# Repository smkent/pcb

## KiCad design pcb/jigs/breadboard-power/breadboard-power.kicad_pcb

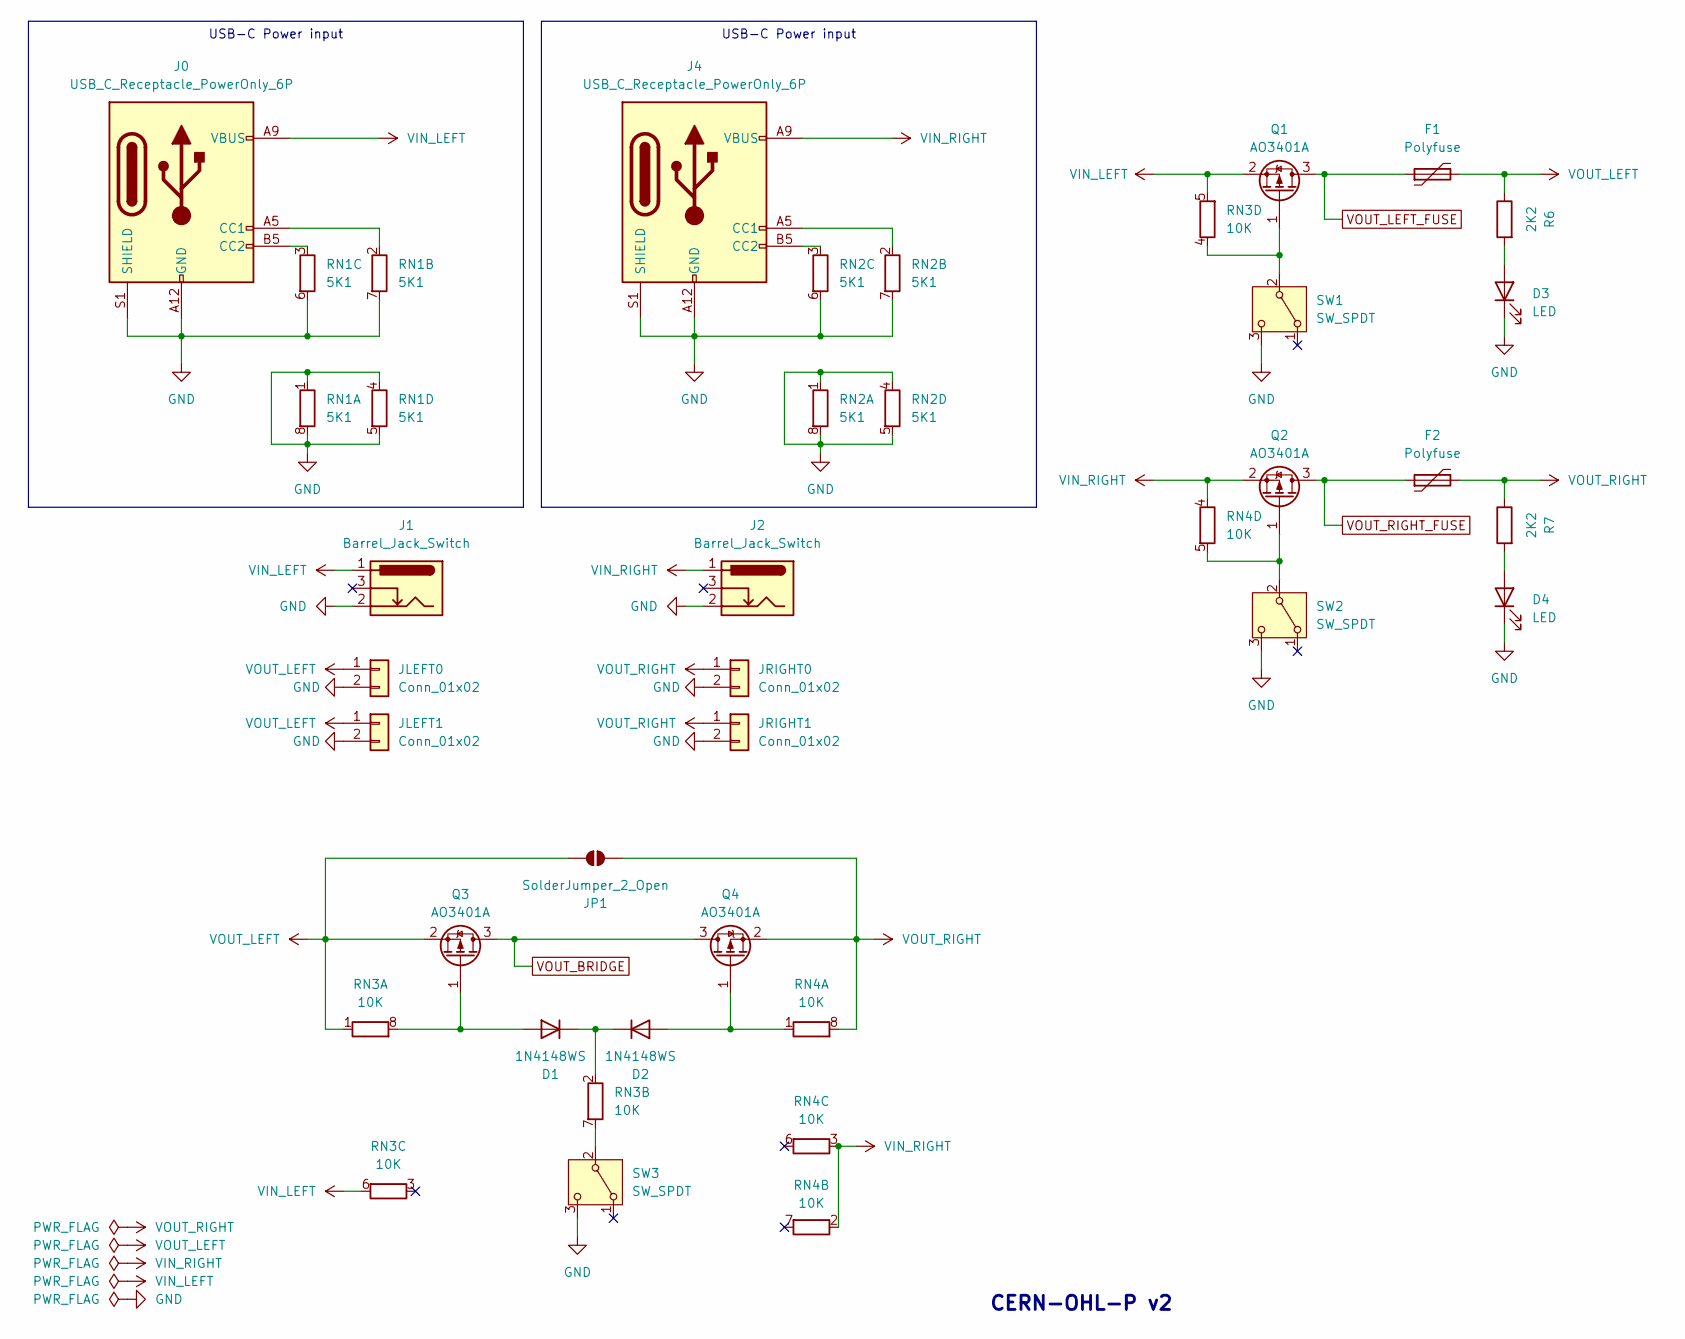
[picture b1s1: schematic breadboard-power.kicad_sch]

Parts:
D1, D2: 1N4148WS; D_SOD-323_HandSoldering
D3, D4: LED; LED_0805_2012Metric_Pad1.15x1.40mm_HandSolder_simple
F1, F2: Polyfuse; Fuse_1206_3216Metric
J0, J4: USB_C_Receptacle_PowerOnly_6P; USB_C_Receptacle_GCT_USB4125-xx-x_6P_TopMnt_Horizontal_Hand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
J1, J2: Barrel_Jack_Switch; Conn_Combo_DC-050_TerminalBlock_JST-XH-2P-horizontal-TH-or-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
JLEFT0, JLEFT1: Conn_01x02; PinHeader_1x02_P2.54mm_Vertical_simple_pad2gnd
JP1: SolderJumper_2_Open; SolderJumper-2_P1.3mm_Open_RoundedPad1.0x1.5mm_simple
JRIGHT0, JRIGHT1: Conn_01x02; PinHeader_1x02_P2.54mm_Vertical_simple_pad2gnd
Q1, Q2, Q3, Q4: AO3401A; SOT-23; LCSC Part C15127
R6, R7: 2K2; R_0805_2012Metric_Pad1.20x1.40mm_HandSolder
RN1, RN2: 5K1; R_Array_Convex_4x0603
RN3, RN4: 10K; R_Array_Convex_4x0603
SW1, SW2: SW_SPDT; SW_Slide-03_SPDT_P2.50mm_THT; LCSC Part C2998803
SW3: SW_SPDT; SW_SPDT_PCM12; LCSC Part C2998803

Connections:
GND: D3.1 (K), D4.1 (K), J0.A12 (GND), J0.B12 (GND), J0.S1 (SHIELD), J1.2, J2.2, J4.A12 (GND), J4.B12 (GND), J4.S1 (SHIELD), JLEFT0.2, JLEFT1.2, JRIGHT0.2, JRIGHT1.2, RN1.1 (R1.1), RN1.4 (R4.1), RN1.5 (R4.2), RN1.6 (R3.2), RN1.7 (R2.2), RN1.8 (R1.2), RN2.1 (R1.1), RN2.4 (R4.1), RN2.5 (R4.2), RN2.6 (R3.2), RN2.7 (R2.2), RN2.8 (R1.2), SW1.3 (C), SW2.3 (C), SW3.3 (C)
unnamed: D1.2 (A), Q3.1 (G), RN3.8 (R1.2)
unnamed: D1.1 (K), D2.1 (K), RN3.2 (R2.1)
unnamed: D2.2 (A), Q4.1 (G), RN4.1 (R1.1)
unnamed: D3.2 (A), R6.2
unnamed: D4.2 (A), R7.2
unnamed: J0.A5 (CC1), RN1.2 (R2.1)
unnamed: J0.B5 (CC2), RN1.3 (R3.1)
unnamed: J4.A5 (CC1), RN2.2 (R2.1)
unnamed: J4.B5 (CC2), RN2.3 (R3.1)
unnamed: Q1.1 (G), RN3.4 (R4.1), SW1.2 (B)
unnamed: Q2.1 (G), RN4.5 (R4.2), SW2.2 (B)
unnamed: RN3.7 (R2.2), SW3.2 (B)
VIN_LEFT: J0.A9 (VBUS), J0.B9 (VBUS), J1.1, Q1.2 (S), RN3.5 (R4.2), RN3.6 (R3.2)
VIN_RIGHT: J2.1, J4.A9 (VBUS), J4.B9 (VBUS), Q2.2 (S), RN4.2 (R2.1), RN4.3 (R3.1), RN4.4 (R4.1)
VOUT_BRIDGE: Q3.3 (D), Q4.3 (D)
VOUT_LEFT: F1.2, JLEFT0.1, JLEFT1.1, JP1.1 (A), Q3.2 (S), R6.1, RN3.1 (R1.1)
VOUT_LEFT_FUSE: F1.1, Q1.3 (D)
VOUT_RIGHT: F2.2, JP1.2 (B), JRIGHT0.1, JRIGHT1.1, Q4.2 (S), R7.1, RN4.8 (R1.2)
VOUT_RIGHT_FUSE: F2.1, Q2.3 (D)

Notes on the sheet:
USB-C Power input
CERN-OHL-P v2

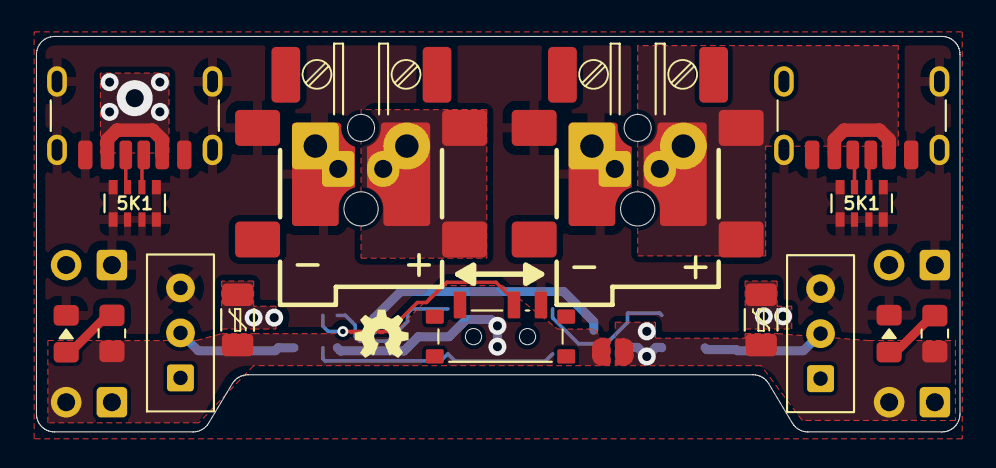
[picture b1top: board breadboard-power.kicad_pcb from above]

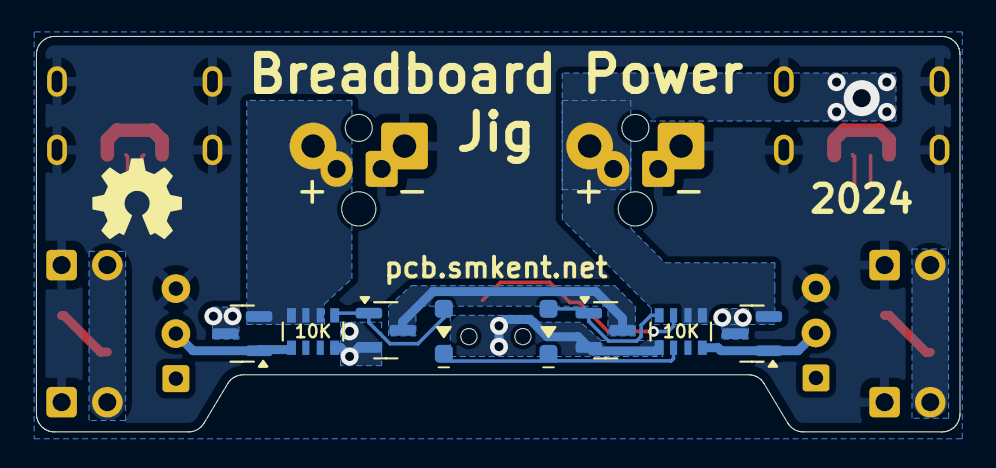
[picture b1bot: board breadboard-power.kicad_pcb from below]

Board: 2 copper layers, 51.3 x 22.0 mm, 28 parts (12 on the bottom side), 20 nets.

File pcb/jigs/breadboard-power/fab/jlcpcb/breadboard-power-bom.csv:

Comment,Designator,Footprint,LCSC
1N4148WS,"D1,D2",custom:D_SOD-323_HandSoldering_simple,
AO3401A,"Q1,Q2,Q3,Q4",Package_TO_SOT_SMD:SOT-23,C15127
SW_SPDT,SW3,lcsc:SW-SMD_3P-P1.50_L2.7-W6.6,C2998803
Conn_01x02,"JLEFT0,JLEFT1,JRIGHT0,JRIGHT1",custom:PinHeader_1x02_P2.54mm_Vertical_simple_pad2gnd,
10K,"RN3,RN4",Resistor_SMD:R_Array_Convex_4x0603,
2K2,"R6,R7",Resistor_SMD:R_0805_2012Metric_Pad1.20x1.40mm_HandSolder,
5K1,"RN1,RN2",Resistor_SMD:R_Array_Convex_4x0603,
Barrel_Jack_Switch,"J1,J2",custom:Conn_Combo_DC-050_TerminalBlock_JST-XH-2P-horizontal-TH-or-SMD_compact,
SW_SPDT,"SW1,SW2",custom:SW-TH_DEALON_SS-12D01-GX_simple,C2998803
Polyfuse,"F1,F2",custom:Fuse_1206_3216Metric_Pad1.42x1.75mm_HandSolder_simple,
LED,"D3,D4",custom:LED_0805_2012Metric_Pad1.15x1.40mm_HandSolder_simple,
USB_C_Receptacle_PowerOnly_6P,"J0,J4",custom:USB_C_Receptacle_GCT_USB4125-xx-x_6P_TopMnt_Horizontal_handsolder,

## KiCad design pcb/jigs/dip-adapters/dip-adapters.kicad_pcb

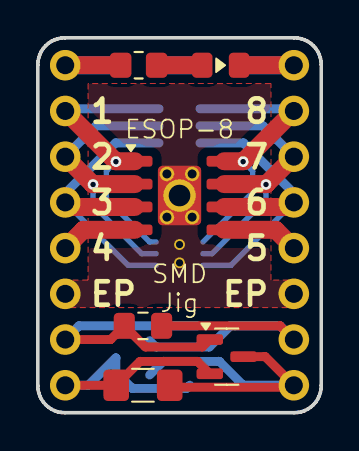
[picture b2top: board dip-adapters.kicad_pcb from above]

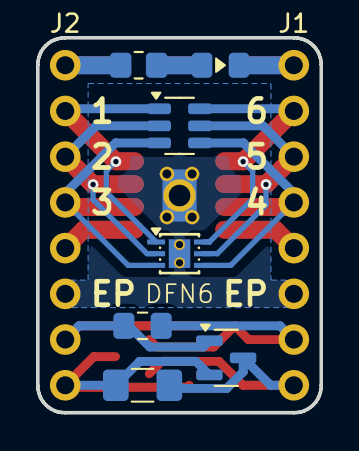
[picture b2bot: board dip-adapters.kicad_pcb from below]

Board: 2 copper layers, 15.7 x 20.8 mm, 15 parts (9 on the bottom side), 17 nets.

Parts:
C1, C2: C; C_0805_2012Metric_Pad1.18x1.45mm_HandSolder
F1, F2: Polyfuse; Fuse_1206_3216Metric_Pad1.42x1.75mm_HandSolder
J1, J2: Conn_01x08; PinHeader_1x08_P2.54mm_Vertical_simple
LED1, LED2: LED; LED_0805_2012Metric_Pad1.15x1.40mm_HandSolder_simple
Q1, Q2: AO3401A; SOT-23
R1, R2: 1K; R_0805_2012Metric_Pad1.20x1.40mm_HandSolder
U1: TP4056; SOIC-8-1EP_3.9x4.9mm_P1.27mm_EP2.41x3.3mm_ThermalVias_Custo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
U2: 1EDN7550B; SOT-23-6
U3: XB6366D; DFN-6_L2.0-W2.0-P0.65-BL-EP_ThermalVias_HandSolder

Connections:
1: J1.2, U1.1 (TEMP), U2.6 (OUT_SNK), U3.6 (VM)
2: J1.3, U1.2 (PROG), U2.5 (OUT_SRC), U3.5 (VM)
3: J1.4, U1.3 (GND), U2.4 (VDD), U3.4 (VM)
4: J1.5, U1.4 (VCC)
5: J2.5, U1.5 (BAT)
6: J2.4, U1.6 (~STDBY), U2.3 (IN+), U3.3 (GND)
7: J2.3, U1.7 (~CHRG), U2.2 (GND), U3.2 (GND)
8: J2.2, U1.8 (CE), U2.1 (IN-), U3.1 (VDD)
EP: J1.6, J2.6, U1.9 (EP), U3.7 (EP)
L7: C1.1, C2.1, J2.7, Q2.1 (G)
L8: F1.1, F2.1, J2.8, Q1.3 (D), Q2.2 (S)
unnamed: J1.1, LED2.1 (K), R2.1
unnamed: J2.1, LED1.1 (K), R1.1
unnamed: LED1.2 (A), R2.2
unnamed: LED2.2 (A), R1.2
R7: C1.2, C2.2, J1.7, Q1.1 (G)
R8: F1.2, F2.2, J1.8, Q1.2 (S), Q2.3 (D)

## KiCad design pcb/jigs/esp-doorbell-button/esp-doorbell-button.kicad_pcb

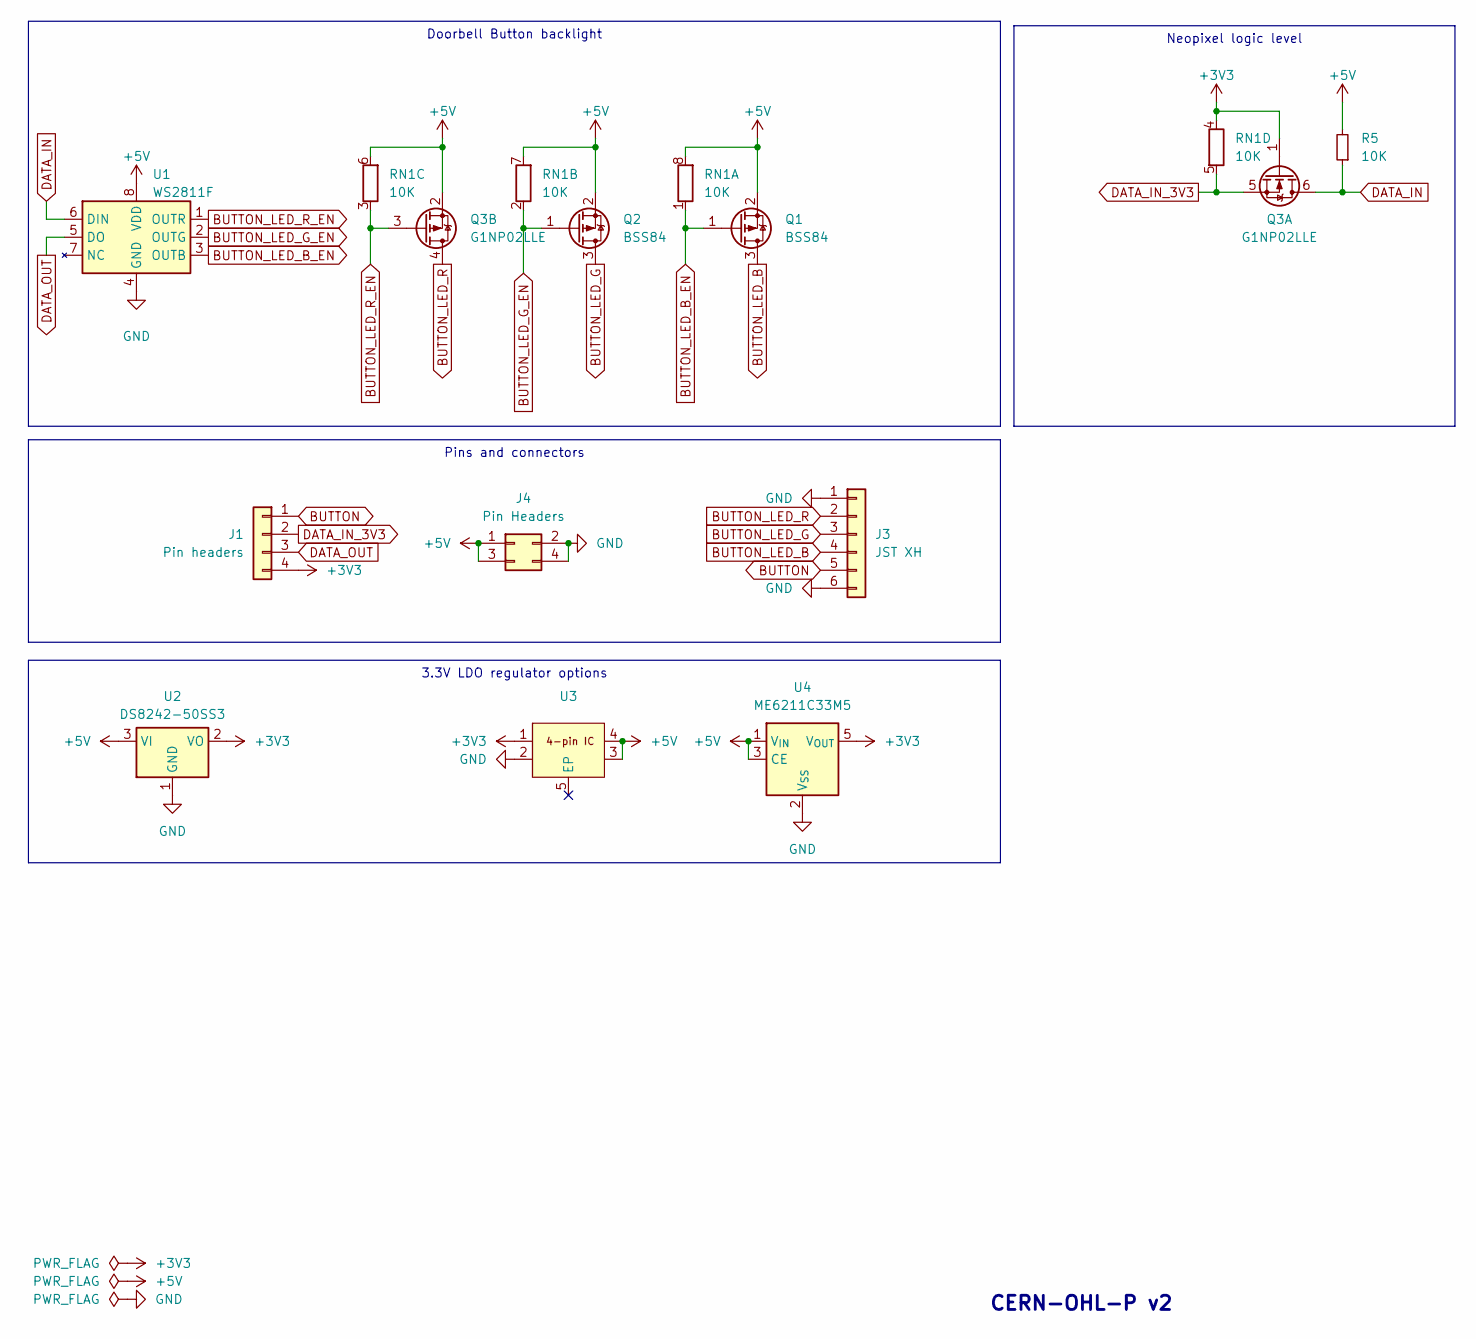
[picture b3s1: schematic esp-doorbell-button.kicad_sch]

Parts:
J1: Pin headers; PinHeader_1x04_P2.54mm_Vertical_simple
J3: JST XH; JST_XH_B6B-XH-A_1x06_P2.50mm_Vertical
J4: Pin Headers; PinHeader_2x02_P2.54mm_Vertical_simple
Q1, Q2: BSS84; SOT-23
Q3: G1NP02LLE; SOT-23-6; LCSC Part C7465318
R5: 10K; R_0603_1608Metric
RN1: 10K; R_Array_Convex_4x0603
U1: WS2811F; FSOP-8_L3.3-W1.7-P0.80-LS2.9-BL; LCSC Part C5446692
U2: DS8242-50SS3; SOT-23; LCSC Part C5884141
U3: Texas_X2SON-4_1x1mm_P0.65mm
U4: ME6211C33M5; SOT-23-5

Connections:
+3V3: J1.4, Q3.1 (G), RN1.4 (R4.1), U2.2 (VO), U3.1, U4.5 (V_{OUT})
+5V: J4.1, J4.3, Q1.2 (S), Q2.2 (S), Q3.2 (S), R5.2, RN1.6 (R3.2), RN1.7 (R2.2), RN1.8 (R1.2), U1.8 (VDD), U2.3 (VI), U3.3, U3.4, U4.1 (V_{IN}), U4.3 (CE)
BUTTON: J1.1, J3.5
BUTTON_LED_B: J3.4, Q1.3 (D)
BUTTON_LED_B_EN: Q1.1 (G), RN1.1 (R1.1), U1.3 (OUTB)
BUTTON_LED_G: J3.3, Q2.3 (D)
BUTTON_LED_G_EN: Q2.1 (G), RN1.2 (R2.1), U1.2 (OUTG)
BUTTON_LED_R: J3.2, Q3.4 (D)
BUTTON_LED_R_EN: Q3.3 (G), RN1.3 (R3.1), U1.1 (OUTR)
DATA_IN: Q3.6 (D), R5.1, U1.6 (DIN)
DATA_IN_3V3: J1.2, Q3.5 (S), RN1.5 (R4.2)
DATA_OUT: J1.3, U1.5 (DO)
GND: J3.1, J3.6, J4.2, J4.4, U1.4 (GND), U2.1 (GND), U3.2, U4.2 (V_{SS})

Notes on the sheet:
Neopixel logic level
3.3V LDO regulator options
Pins and connectors
Doorbell Button backlight
CERN-OHL-P v2

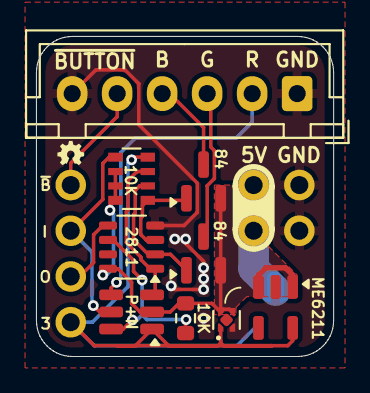
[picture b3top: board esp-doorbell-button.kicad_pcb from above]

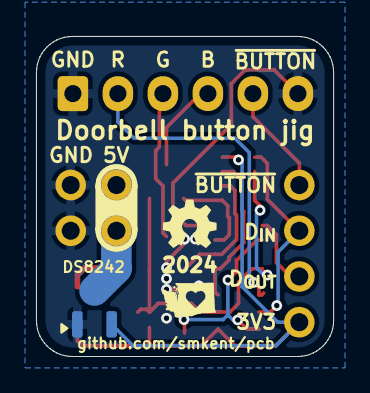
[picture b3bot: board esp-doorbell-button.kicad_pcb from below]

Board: 2 copper layers, 16.5 x 17.8 mm, 12 parts (3 on the bottom side), 13 nets.

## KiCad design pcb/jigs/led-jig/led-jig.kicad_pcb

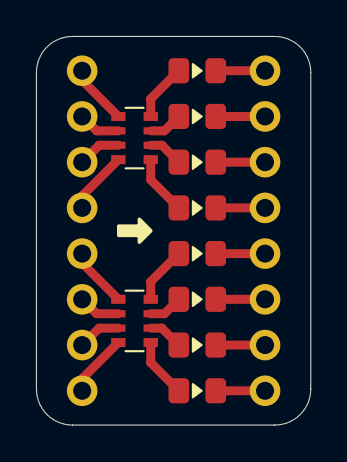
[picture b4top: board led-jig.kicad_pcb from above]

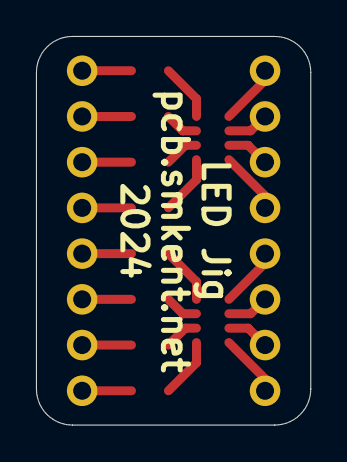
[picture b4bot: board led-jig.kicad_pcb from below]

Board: 2 copper layers, 15.2 x 21.6 mm, 12 parts (2 on the bottom side), 24 nets.

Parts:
J1, J2: Conn_01x08; PinHeader_1x08_P2.54mm_Vertical_simple
LED1, LED2, LED3, LED4, LED5, LED6, LED7, LED8: LED; LED_0805_2012Metric_Pad1.15x1.40mm_HandSolder_simple
RN1, RN2: R_Pack04_Split; R_Array_Convex_4x0603

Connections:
LED1: J1.1, RN1.1 (R1.1)
LED1_OUT: J2.1, LED1.1 (K)
LED2: J1.2, RN1.2 (R2.1)
LED2_OUT: J2.2, LED2.1 (K)
LED3: J1.3, RN1.3 (R3.1)
LED3_OUT: J2.3, LED3.1 (K)
LED4: J1.4, RN1.4 (R4.1)
LED4_OUT: J2.4, LED4.1 (K)
LED5: J1.5, RN2.1 (R1.1)
LED5_OUT: J2.5, LED5.1 (K)
LED6: J1.6, RN2.2 (R2.1)
LED6_OUT: J2.6, LED6.1 (K)
LED7: J1.7, RN2.3 (R3.1)
LED7_OUT: J2.7, LED7.1 (K)
LED8: J1.8, RN2.4 (R4.1)
LED8_OUT: J2.8, LED8.1 (K)
unnamed: LED1.2 (A), RN1.8 (R1.2)
unnamed: LED2.2 (A), RN1.7 (R2.2)
unnamed: LED3.2 (A), RN1.6 (R3.2)
unnamed: LED4.2 (A), RN1.5 (R4.2)
unnamed: LED5.2 (A), RN2.8 (R1.2)
unnamed: LED6.2 (A), RN2.7 (R2.2)
unnamed: LED7.2 (A), RN2.6 (R3.2)
unnamed: LED8.2 (A), RN2.5 (R4.2)

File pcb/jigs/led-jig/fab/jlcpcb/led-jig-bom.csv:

Comment,Designator,Footprint,LCSC
LED,"LED1,LED2,LED3,LED4,LED5,LED6,LED7,LED8",custom:LED_0805_2012Metric_Pad1.15x1.40mm_HandSolder_simple,
Conn_01x08,"J1,J2",custom:PinHeader_1x08_P2.54mm_Vertical_simple,
R_Pack04_Split,"RN1,RN2",Resistor_SMD:R_Array_Convex_4x0603,

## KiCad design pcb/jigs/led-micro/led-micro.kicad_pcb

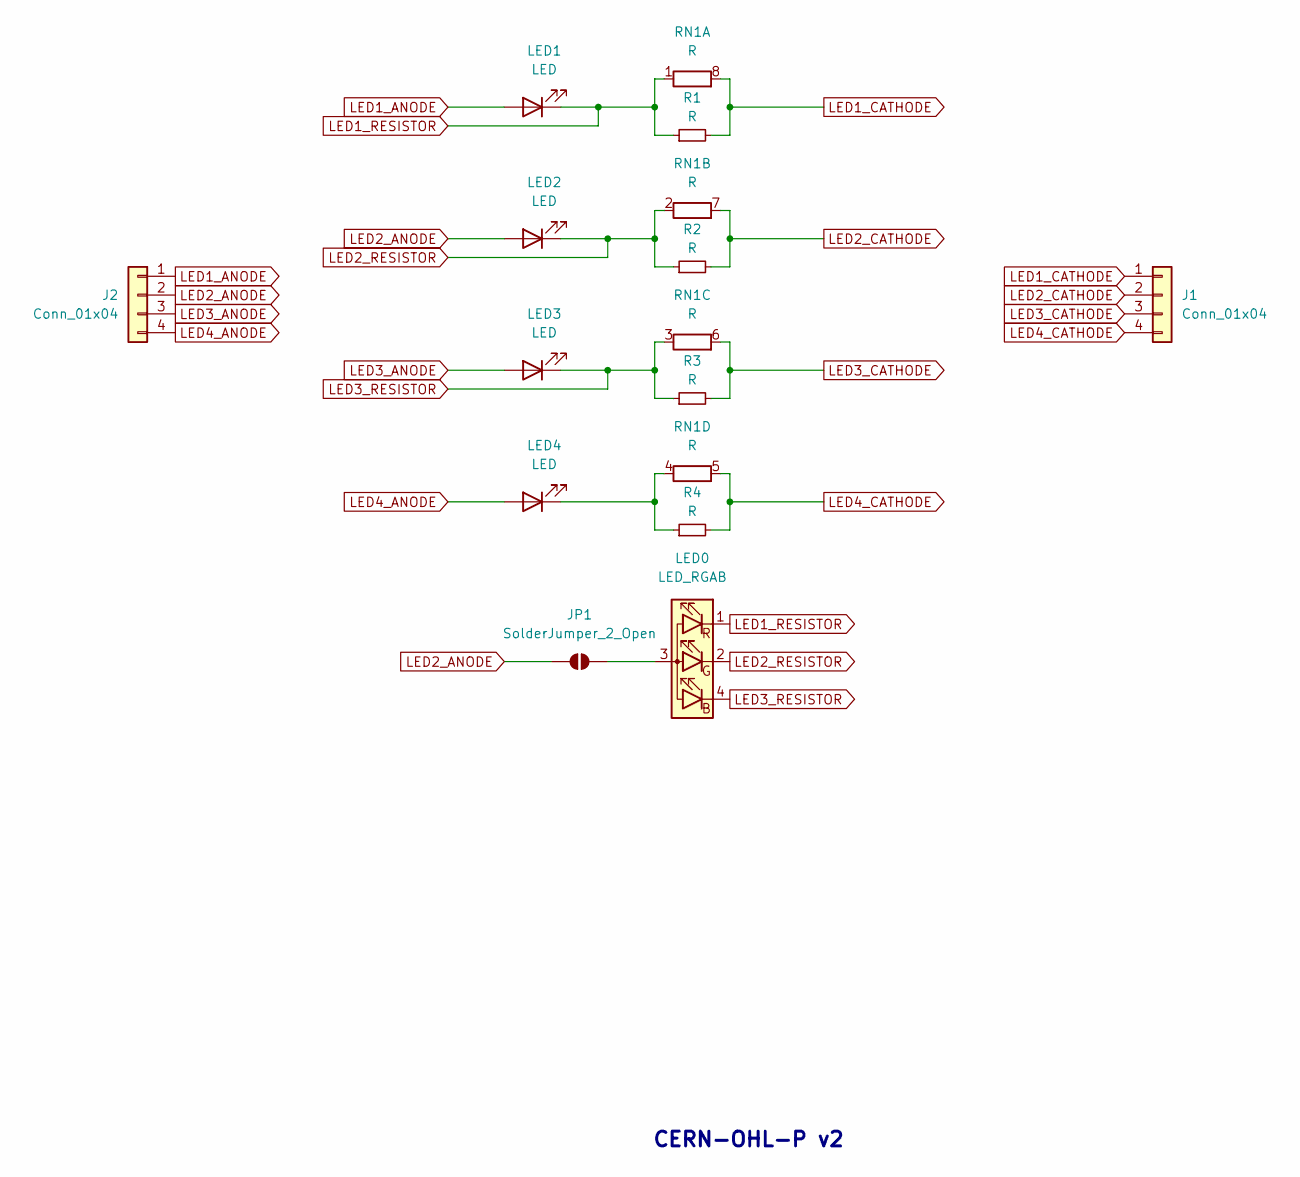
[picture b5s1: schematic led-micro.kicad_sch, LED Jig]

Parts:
J1, J2: Conn_01x04; PinHeader_1x04_P2.54mm_Vertical_simple
JP1: SolderJumper_2_Open; SolderJumper-2_P1.3mm_Open_TrianglePad1.0x1.5mm
LED0: LED_RGAB; LED_RGB_XL-2012RGBC_2.0x1.2mm_HandSolder; LCSC Part C965848
LED1, LED2, LED3, LED4: LED; LED_0805_2012Metric_Pad1.15x1.40mm_HandSolder_simple
R1, R2, R3, R4: R; R_0805_2012Metric_Pad1.20x1.40mm_HandSolder
RN1: R; R_Array_Convex_4x0603

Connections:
LED1_ANODE: J2.1, LED1.2 (A)
LED1_CATHODE: J1.1, R1.2, RN1.8 (R1.2)
LED1_RESISTOR: LED0.1 (RK), LED1.1 (K), R1.1, RN1.1 (R1.1)
LED2_ANODE: J2.2, JP1.1 (A), LED2.2 (A)
LED2_CATHODE: J1.2, R2.2, RN1.7 (R2.2)
LED2_RESISTOR: LED0.2 (GK), LED2.1 (K), R2.1, RN1.2 (R2.1)
LED3_ANODE: J2.3, LED3.2 (A)
LED3_CATHODE: J1.3, R3.2, RN1.6 (R3.2)
LED3_RESISTOR: LED0.4 (BK), LED3.1 (K), R3.1, RN1.3 (R3.1)
LED4_ANODE: J2.4, LED4.2 (A)
LED4_CATHODE: J1.4, R4.2, RN1.5 (R4.2)
unnamed: JP1.2 (B), LED0.3 (A)
unnamed: LED4.1 (K), R4.1, RN1.4 (R4.1)

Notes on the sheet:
CERN-OHL-P v2

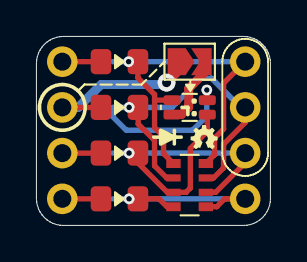
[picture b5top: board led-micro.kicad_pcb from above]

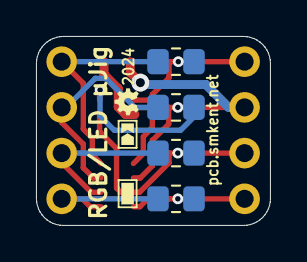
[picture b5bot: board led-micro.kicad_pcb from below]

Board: 2 copper layers, 13.0 x 10.5 mm, 13 parts (6 on the bottom side), 13 nets.

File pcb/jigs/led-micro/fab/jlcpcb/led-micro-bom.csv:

Comment,Designator,Footprint,LCSC
LED,"LED1,LED2,LED3,LED4",custom:LED_0805_2012Metric_Pad1.15x1.40mm_HandSolder_simple,
R,"R1,R2,R3,R4",Resistor_SMD:R_0805_2012Metric_Pad1.20x1.40mm_HandSolder,
R,RN1,Resistor_SMD:R_Array_Convex_4x0603,
LED_RGAB,LED0,lcsc:LED-ARRAY-SMD_4P-L2.0-W1.3-BR_HandSolder,C965848
Conn_01x04,"J1,J2",custom:PinHeader_1x04_P2.54mm_Vertical_simple,

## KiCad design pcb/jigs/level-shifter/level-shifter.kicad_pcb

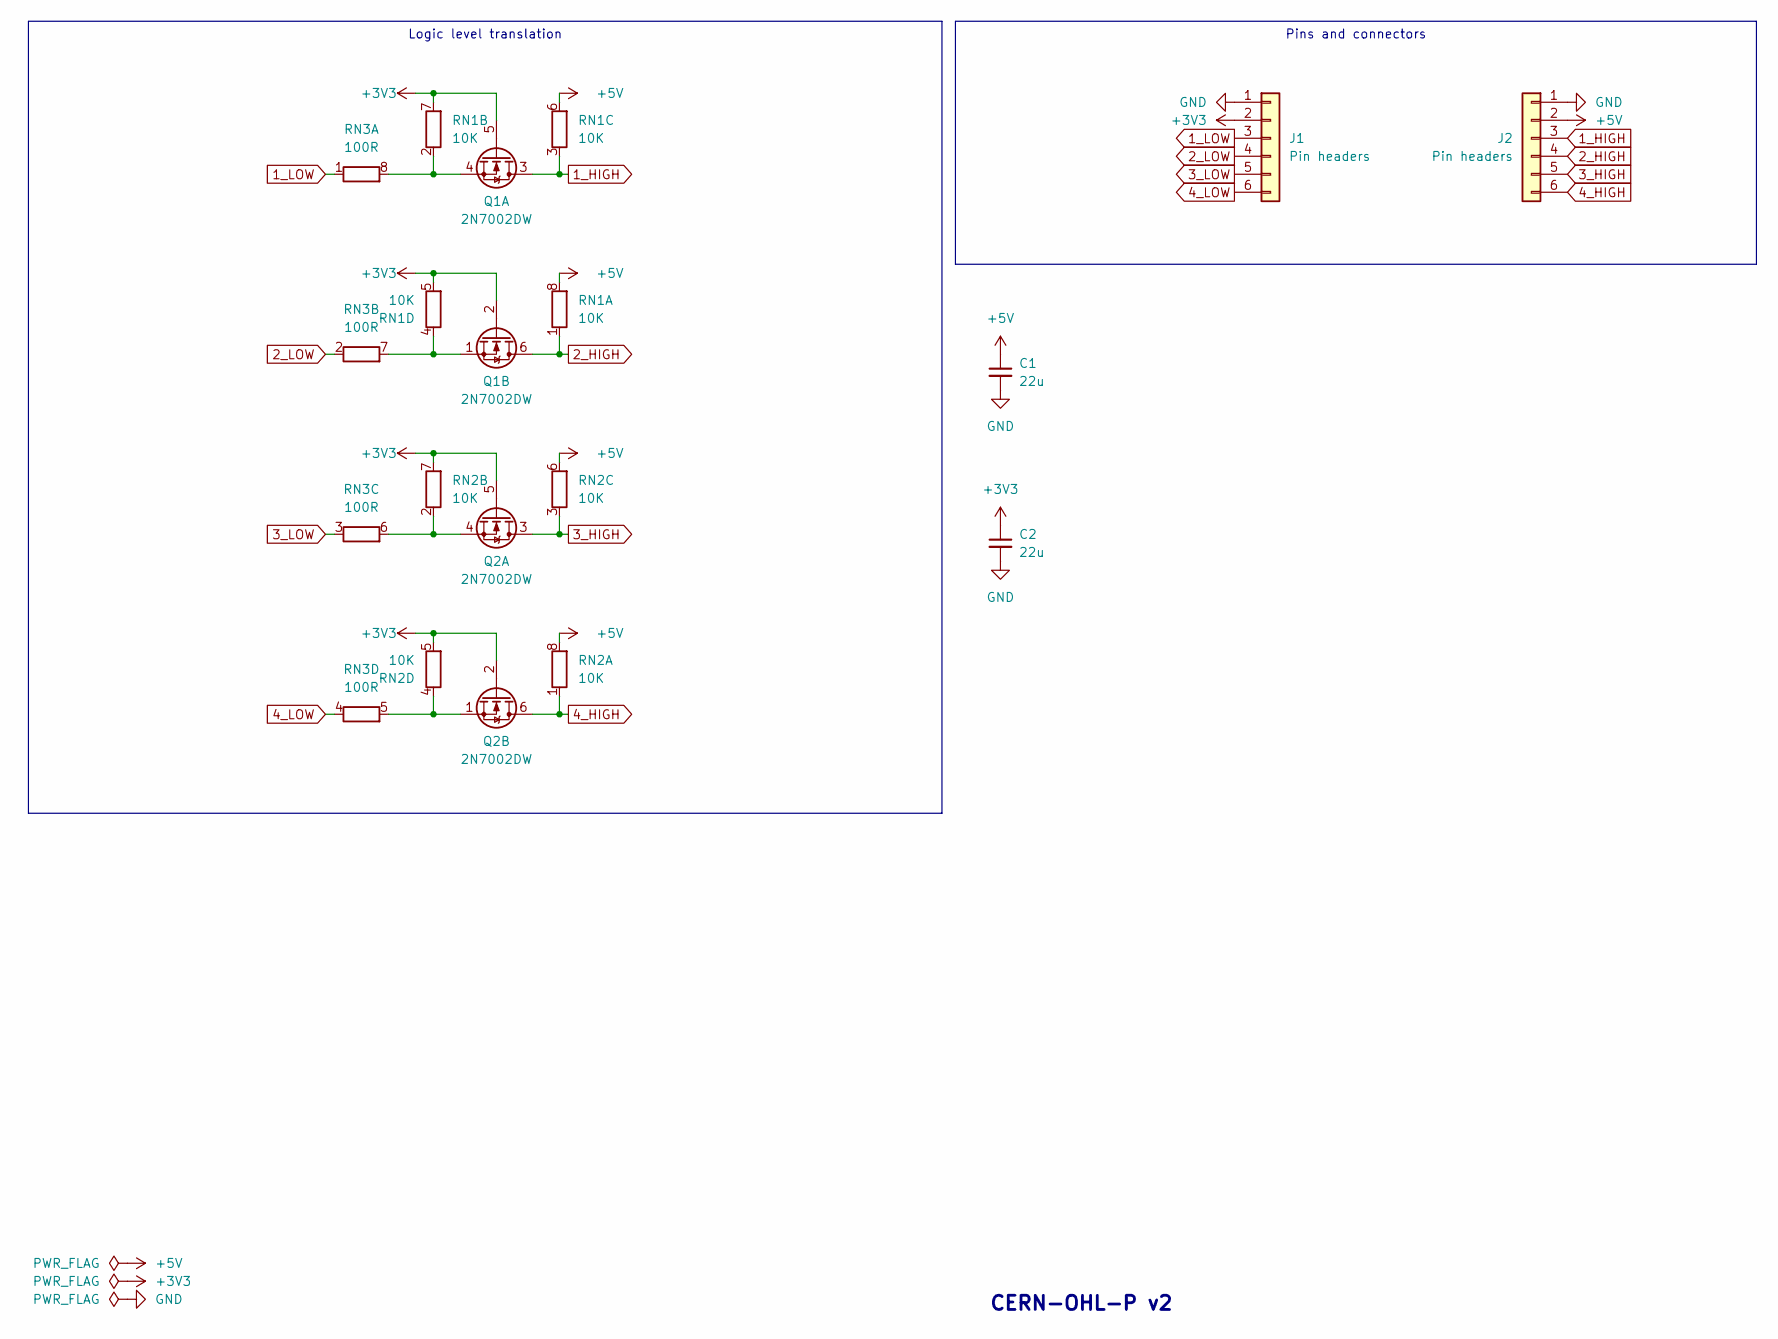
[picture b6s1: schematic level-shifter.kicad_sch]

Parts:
C1, C2: 22u; C_0603_1608Metric_Pad1.08x0.95mm_HandSolder
J1, J2: Pin headers; PinHeader_1x06_P2.54mm_Vertical_simple_pad1gnd
Q1, Q2: 2N7002DW; SOT-363_SC-70-6; LCSC Part C5190214
RN1, RN2: 10K; R_Array_Convex_4x0603
RN3: 100R; R_Array_Convex_4x0603

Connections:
1_HIGH: J2.3, Q1.3 (D), RN1.3 (R3.1)
1_LOW: J1.3, RN3.1 (R1.1)
2_HIGH: J2.4, Q1.6 (D), RN1.1 (R1.1)
2_LOW: J1.4, RN3.2 (R2.1)
3_HIGH: J2.5, Q2.3 (D), RN2.3 (R3.1)
3_LOW: J1.5, RN3.3 (R3.1)
4_HIGH: J2.6, Q2.6 (D), RN2.1 (R1.1)
4_LOW: J1.6, RN3.4 (R4.1)
+3V3: C2.1, J1.2, Q1.2 (G), Q1.5 (G), Q2.2 (G), Q2.5 (G), RN1.5 (R4.2), RN1.7 (R2.2), RN2.5 (R4.2), RN2.7 (R2.2)
+5V: C1.1, J2.2, RN1.6 (R3.2), RN1.8 (R1.2), RN2.6 (R3.2), RN2.8 (R1.2)
GND: C1.2, C2.2, J1.1, J2.1
unnamed: Q1.4 (S), RN1.2 (R2.1), RN3.8 (R1.2)
unnamed: Q1.1 (S), RN1.4 (R4.1), RN3.7 (R2.2)
unnamed: Q2.4 (S), RN2.2 (R2.1), RN3.6 (R3.2)
unnamed: Q2.1 (S), RN2.4 (R4.1), RN3.5 (R4.2)

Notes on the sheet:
Pins and connectors
Logic level translation
CERN-OHL-P v2

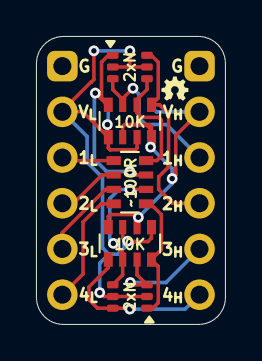
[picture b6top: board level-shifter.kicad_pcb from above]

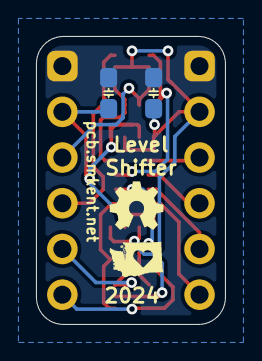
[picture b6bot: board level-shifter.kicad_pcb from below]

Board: 2 copper layers, 10.5 x 16.0 mm, 9 parts (4 on the bottom side), 15 nets.

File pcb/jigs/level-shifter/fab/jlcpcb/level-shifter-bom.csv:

Comment,Designator,Footprint,LCSC
Pin headers,"J1,J2",custom:PinHeader_1x06_P2.54mm_Vertical_simple_pad1gnd,
2N7002DW,"Q1,Q2",custom:SOT-363_SC-70-6_simple,C5190214
100R,RN3,Resistor_SMD:R_Array_Convex_4x0603,
10K,"RN1,RN2",Resistor_SMD:R_Array_Convex_4x0603,
22u,"C1,C2",custom:C_0603_1608Metric_Pad1.08x0.95mm_HandSolder,

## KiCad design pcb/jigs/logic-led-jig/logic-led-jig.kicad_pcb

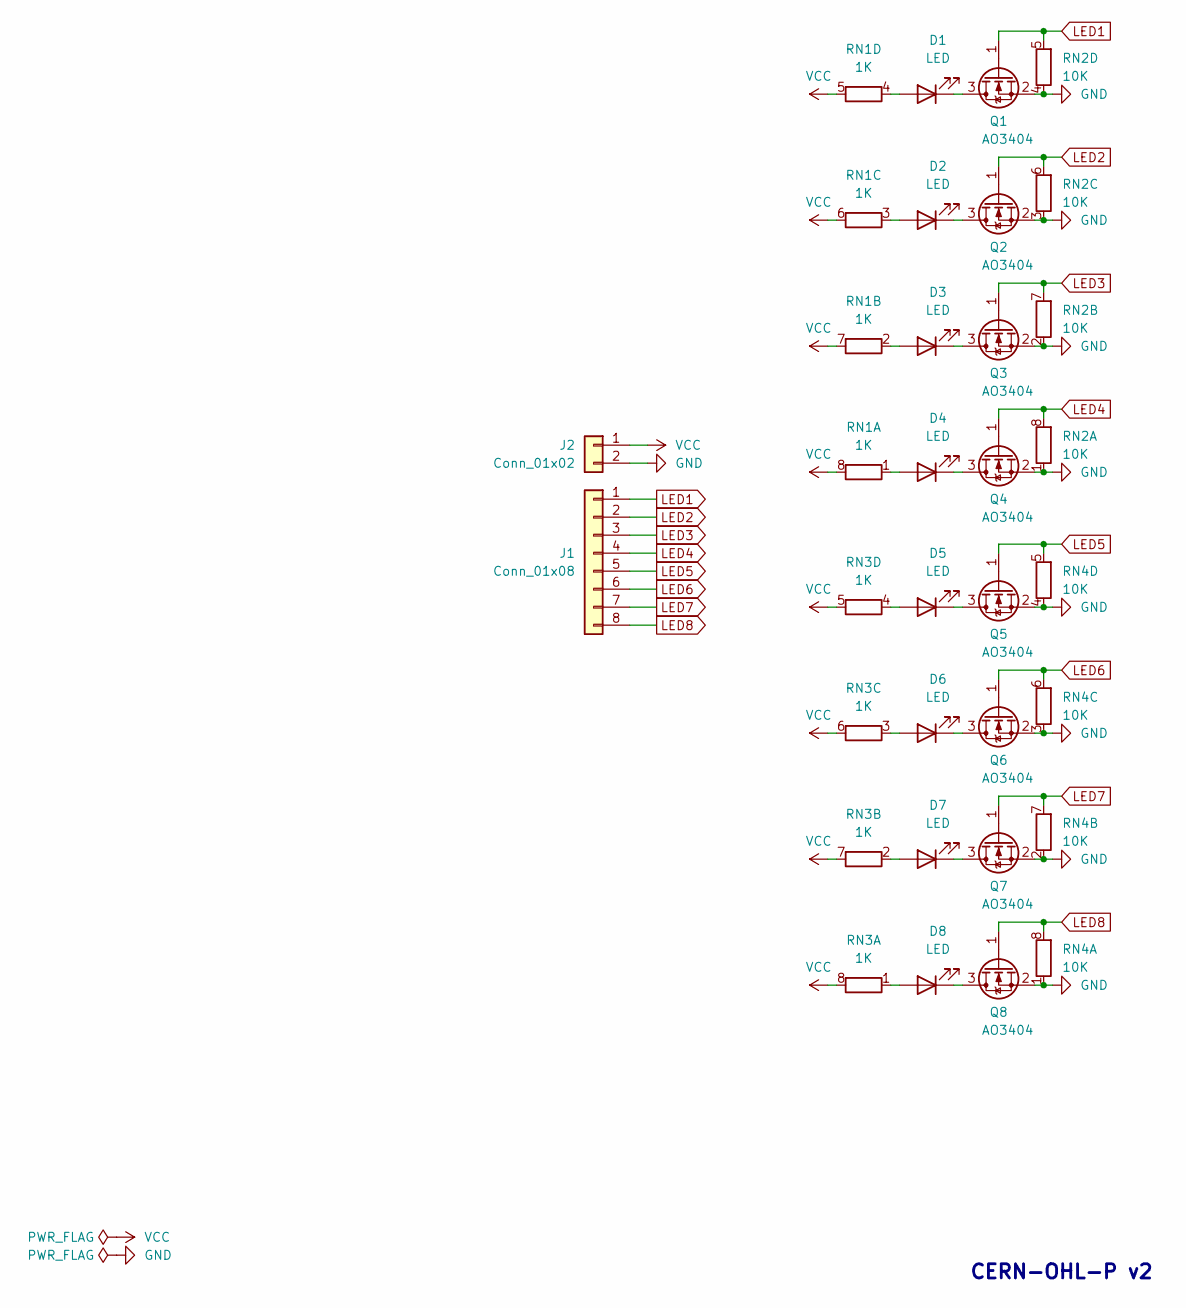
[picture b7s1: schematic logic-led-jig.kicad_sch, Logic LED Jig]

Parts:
D1, D2, D3, D4, D5, D6, D7, D8: LED; LED_0805_2012Metric
J1: Conn_01x08; PinHeader_1x08_P2.54mm_Vertical_simple
J2: Conn_01x02; PinHeader_1x02_P2.54mm_Vertical_simple_pad2gnd
Q1, Q2, Q3, Q4, Q5, Q6, Q7, Q8: AO3404; SOT-23
RN1, RN3: 1K; R_Array_Convex_4x0603
RN2, RN4: 10K; R_Array_Convex_4x0603

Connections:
GND: J2.2, Q1.2 (S), Q2.2 (S), Q3.2 (S), Q4.2 (S), Q5.2 (S), Q6.2 (S), Q7.2 (S), Q8.2 (S), RN2.1 (R1.1), RN2.2 (R2.1), RN2.3 (R3.1), RN2.4 (R4.1), RN4.1 (R1.1), RN4.2 (R2.1), RN4.3 (R3.1), RN4.4 (R4.1)
LED1: J1.1, Q1.1 (G), RN2.5 (R4.2)
LED2: J1.2, Q2.1 (G), RN2.6 (R3.2)
LED3: J1.3, Q3.1 (G), RN2.7 (R2.2)
LED4: J1.4, Q4.1 (G), RN2.8 (R1.2)
LED5: J1.5, Q5.1 (G), RN4.5 (R4.2)
LED6: J1.6, Q6.1 (G), RN4.6 (R3.2)
LED7: J1.7, Q7.1 (G), RN4.7 (R2.2)
LED8: J1.8, Q8.1 (G), RN4.8 (R1.2)
unnamed: D1.2 (A), RN1.4 (R4.1)
unnamed: D1.1 (K), Q1.3 (D)
unnamed: D2.2 (A), RN1.3 (R3.1)
unnamed: D2.1 (K), Q2.3 (D)
unnamed: D3.2 (A), RN1.2 (R2.1)
unnamed: D3.1 (K), Q3.3 (D)
unnamed: D4.2 (A), RN1.1 (R1.1)
unnamed: D4.1 (K), Q4.3 (D)
unnamed: D5.2 (A), RN3.4 (R4.1)
unnamed: D5.1 (K), Q5.3 (D)
unnamed: D6.2 (A), RN3.3 (R3.1)
unnamed: D6.1 (K), Q6.3 (D)
unnamed: D7.2 (A), RN3.2 (R2.1)
unnamed: D7.1 (K), Q7.3 (D)
unnamed: D8.2 (A), RN3.1 (R1.1)
unnamed: D8.1 (K), Q8.3 (D)
VCC: J2.1, RN1.5 (R4.2), RN1.6 (R3.2), RN1.7 (R2.2), RN1.8 (R1.2), RN3.5 (R4.2), RN3.6 (R3.2), RN3.7 (R2.2), RN3.8 (R1.2)

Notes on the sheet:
CERN-OHL-P v2

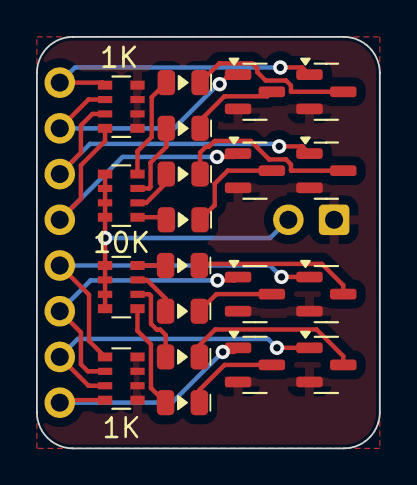
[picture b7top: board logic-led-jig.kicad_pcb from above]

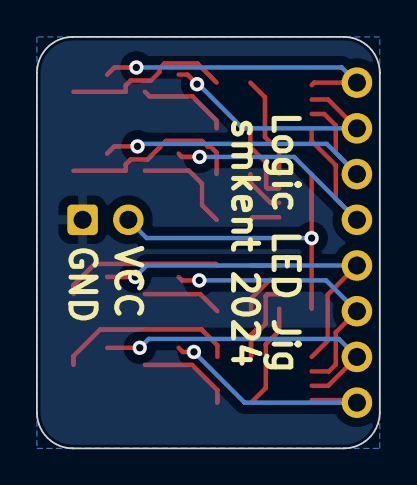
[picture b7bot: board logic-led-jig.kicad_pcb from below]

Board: 2 copper layers, 19.1 x 22.9 mm, 22 parts (2 on the bottom side), 26 nets.

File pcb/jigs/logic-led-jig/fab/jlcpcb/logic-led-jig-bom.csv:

Comment,Designator,Footprint,LCSC
Conn_01x08,J1,custom:PinHeader_1x08_P2.54mm_Vertical_simple,
LED,"D1,D2,D3,D4,D5,D6,D7,D8",custom:LED_0805_2012Metric_simple,
AO3404	,"Q1,Q2,Q3,Q4,Q5,Q6,Q7,Q8",Package_TO_SOT_SMD:SOT-23,
Conn_01x02,J2,custom:PinHeader_1x02_P2.54mm_Vertical_simple_pad2gnd,
10K,"RN2,RN4",Resistor_SMD:R_Array_Convex_4x0603,
1K,"RN1,RN3",Resistor_SMD:R_Array_Convex_4x0603,

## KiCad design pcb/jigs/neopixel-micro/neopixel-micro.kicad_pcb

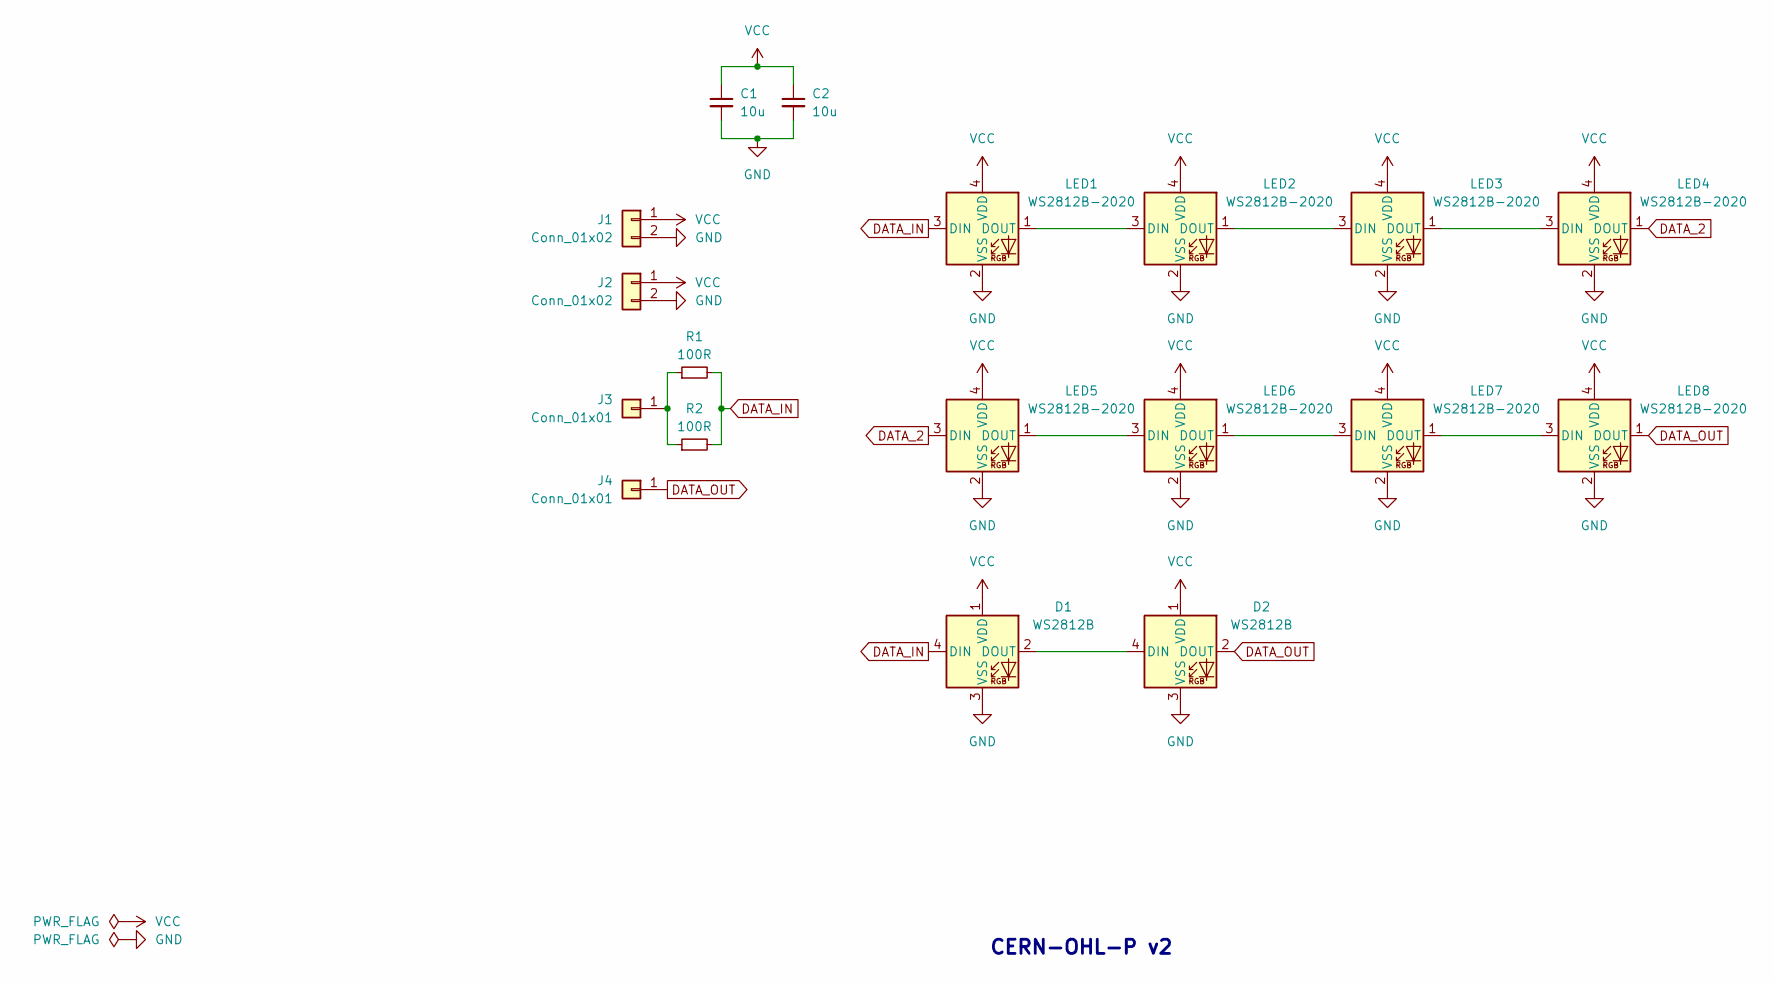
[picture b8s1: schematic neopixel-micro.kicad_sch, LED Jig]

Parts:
C1, C2: 10u; C_0603_1608Metric_Pad1.08x0.95mm_HandSolder
D1, D2: WS2812B; LED_WS2812B_PLCC4_5.0x5.0mm_P3.2mm
J1, J2: Conn_01x02; PinHeader_1x02_P2.54mm_Vertical_simple
J3, J4: Conn_01x01; PinHeader_1x01_P2.54mm_simple
LED1, LED2, LED3, LED4, LED5, LED6, LED7, LED8: WS2812B-2020; LED_WS2812B-2020_PLCC4_2.0x2.0mm_HandSolder
R1, R2: 100R; R_0603_1608Metric_Pad0.98x0.95mm_HandSolder

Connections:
DATA_2: LED4.1 (DOUT), LED5.3 (DIN)
DATA_IN: D1.4 (DIN), LED1.3 (DIN), R1.2, R2.2
DATA_OUT: D2.2 (DOUT), J4.1, LED8.1 (DOUT)
GND: C1.2, C2.2, D1.3 (VSS), D2.3 (VSS), J1.2, J2.2, LED1.2 (VSS), LED2.2 (VSS), LED3.2 (VSS), LED4.2 (VSS), LED5.2 (VSS), LED6.2 (VSS), LED7.2 (VSS), LED8.2 (VSS)
unnamed: D1.2 (DOUT), D2.4 (DIN)
unnamed: J3.1, R1.1, R2.1
unnamed: LED1.1 (DOUT), LED2.3 (DIN)
unnamed: LED2.1 (DOUT), LED3.3 (DIN)
unnamed: LED3.1 (DOUT), LED4.3 (DIN)
unnamed: LED5.1 (DOUT), LED6.3 (DIN)
unnamed: LED6.1 (DOUT), LED7.3 (DIN)
unnamed: LED7.1 (DOUT), LED8.3 (DIN)
VCC: C1.1, C2.1, D1.1 (VDD), D2.1 (VDD), J1.1, J2.1, LED1.4 (VDD), LED2.4 (VDD), LED3.4 (VDD), LED4.4 (VDD), LED5.4 (VDD), LED6.4 (VDD), LED7.4 (VDD), LED8.4 (VDD)

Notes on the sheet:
CERN-OHL-P v2
